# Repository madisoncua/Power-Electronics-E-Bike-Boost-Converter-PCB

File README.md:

Electric Bike Motor Boost Converter KiCad Files
Madison Cua, Tanvi Nikam, and Kellen Cao

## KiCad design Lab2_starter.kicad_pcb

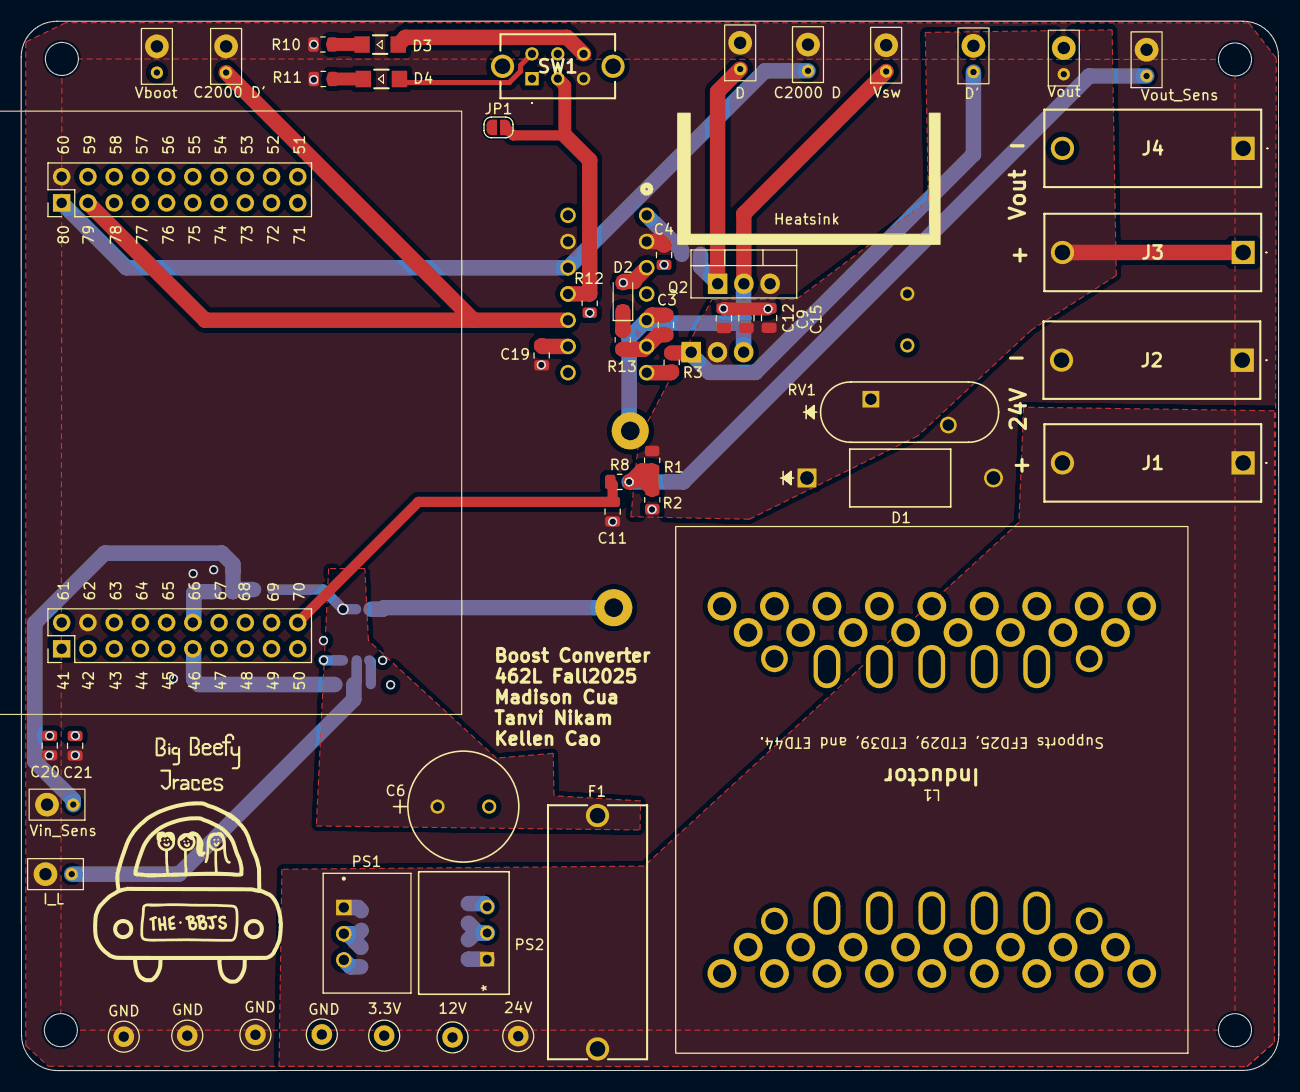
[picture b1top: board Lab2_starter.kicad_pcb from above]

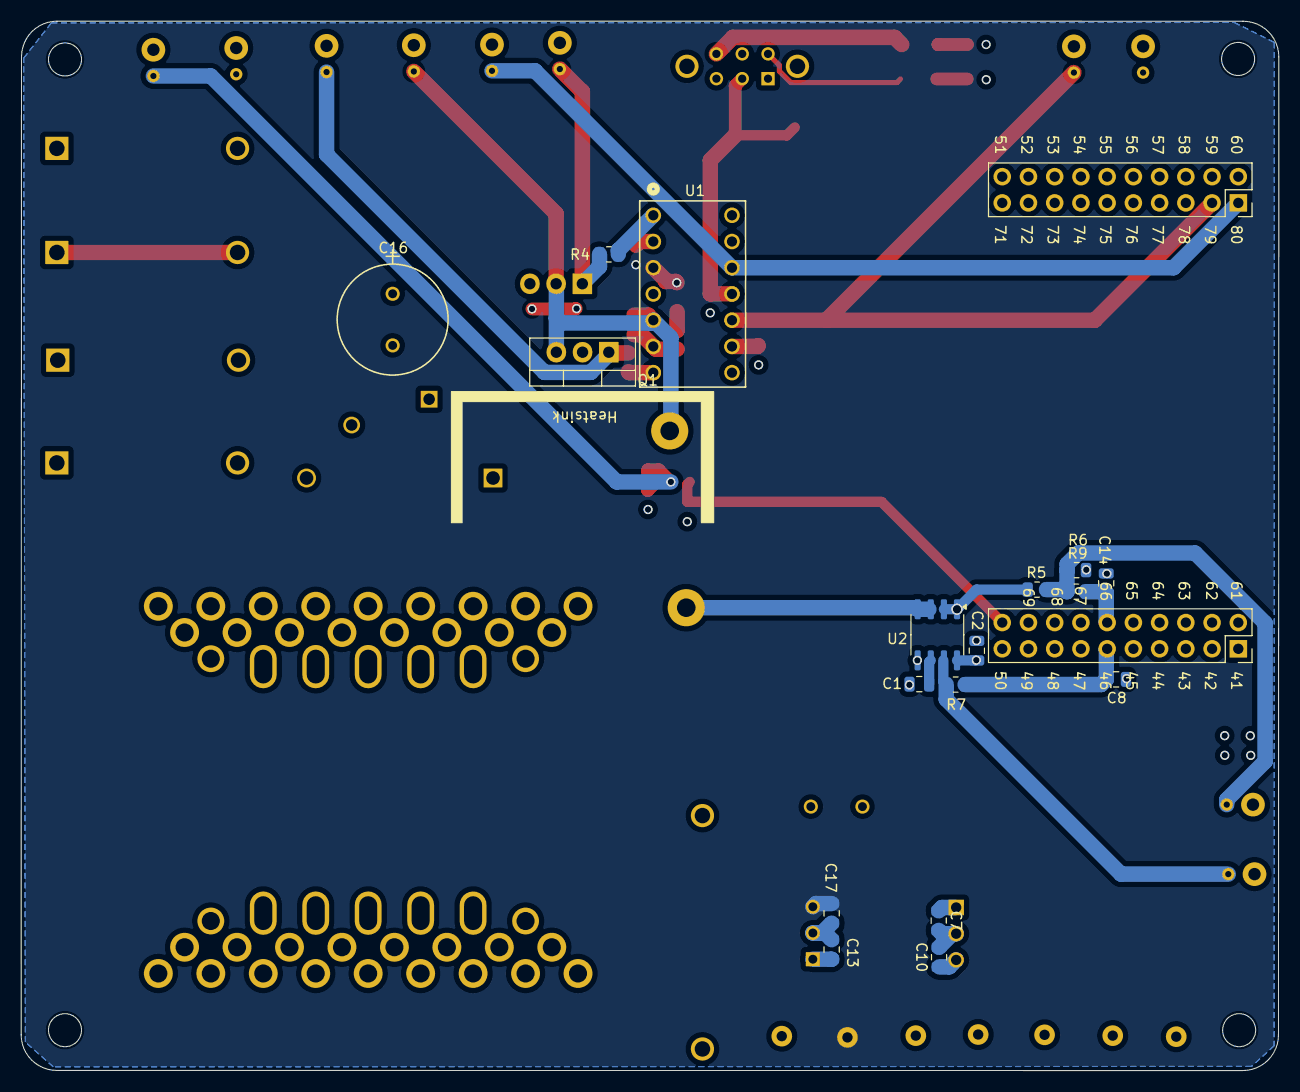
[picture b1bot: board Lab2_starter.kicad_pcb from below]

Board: 4 copper layers, 121.8 x 101.6 mm, 77 parts (18 on the bottom side), 28 nets.

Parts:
3.3V, 12V, 24V: TestPoint; TestPoint_Loop_D1.80mm_Drill1.0mm_Beaded
C1: 100 pF; C_0805_2012Metric
C2, C4, C12, C20: 0.1μF; C_0805_2012Metric
C3: C; C_0805_2012Metric
C6, C16: 100uF; 16PX2200MEFC10X20
C7, C10, C13, C17: 10uF; C_0805_2012Metric
C8, C11, C14: 1n; C_0805_2012Metric
C9: 0.01μF; C_0805_2012Metric
C15, C19, C21: 1μF; C_0805_2012Metric
C2000 D, C2000 D': Conn_01x02; TP
D: Conn_01x02; TP
D1: D_Zener; 1.5KE75A
D2: PMEG10020ELR; Nexperia_CFP3_SOD-123W
D3, D4: LED; WL-SMRW_1206_REC
D': Conn_01x02; TP
F1: Fuse; 696108003002
GND: TestPoint; TestPoint_Loop_D1.80mm_Drill1.0mm_Beaded
GND#2, GND#3, GND#4: TestPoint; TestPoint_Loop_D1.80mm_Drill1.0mm_Beaded
H1, H2, H3, H4: MountingHole; MountingHole_3.2mm_M3
HS1, HS2: Heatsink; HSS-B20-NPS-01
I_L: Conn_01x02; TP
J1, J3: 973582101
J2, J4: 973582100
J5, J6: Conn_01x01; Inductor_wire_conn
JP1: SolderJumper_2_Open; SolderJumper-2_P1.3mm_Open_RoundedPad1.0x1.5mm
L1: L; Inductor
PS1: R-78E3.3-1.0
PS2: R-78E12-0.5; R-78E-0.5_RCP
Q1, Q2: NMOS; TO-220-3_Vertical
R1: 47k; R_0805_2012Metric
R2, R6: 3.3k; R_0805_2012Metric
R3, R4: R_Small; R_0805_2012Metric
R5: 22k; R_0805_2012Metric
R7, R8, R9: 100; R_0805_2012Metric
R10, R11, R12: 1k; R_0805_2012Metric
R13: 2 Ohm; R_0805_2012Metric
RV1: Varistor; V100ZA15P
SW1: SW_Push_DPDT; SLW1116297AD
U1: IR2010; 1-2199298-3
U2: CT416-HSN820DR; SOIC-8_3.9x4.9mm_P1.27mm
U3: LAUNCHXL-F28P55X_BottomHalf
Vboot: Conn_01x02; TP
Vin_Sens: Conn_01x02; TP
Vout: Conn_01x02; TP
Vout_Sens: Conn_01x02; TP
Vsw: Conn_01x02; TP

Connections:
+3.3V: 3.3V.1, C2.1, C10.1, C19.1, C20.1, C21.1, PS1.3 (VOUT), R12.2, SW1.1 (A), SW1.5 (B), U1.9 (VDD), U2.8 (VCC), U3.41
+12V: 12V.1, C4.1, C17.1, D2.2 (A), PS2.3 (VOUT), U1.3 (VCC)
+24V: 24V.1, C7.1, C13.1, F1.1, J1.1, PS1.1 (VIN), PS2.1 (VIN)
/ADCINA0: C11.1, R8.1, U3.70
/ADCINA4: C14.1, R9.1, U3.66
/ADCINA9: C8.1, R7.1, U3.46
C2000 D: C2000 D.2, U1.12 (LIN), U3.80
C2000 D': C2000 D'.2, U1.10 (HIN), U3.79
D: D.2, Q2.1 (G), R4.2
D': D'.2, Q1.1 (G), R3.2
GND: C1.2, C2.2, C4.2, C6.2, C7.2, C8.2, C9.2, C10.2, C11.2, C12.2, C13.2, C14.2, C15.2, C16.2, C17.2, C19.2, C20.2, C21.2, C2000 D.1, C2000 D'.1, D.1, D1.2 (A), D'.1, GND.1, GND#2.1, GND#3.1, GND#4.1, I_L.1, J2.1, J4.1, PS1.2 (GND), PS2.2 (GND), Q2.3 (S), R2.2, R6.2, R10.2, R11.2, RV1.2, SW1.3 (C), U1.2 (COM), U1.13 (VSS), U2.5 (GND), U3.60, U3.62, Vboot.1, Vin_Sens.1, Vout.1, Vout_Sens.1, Vsw.1
I_L: I_L.2, R7.2, U2.7 (OUT)
unnamed: D2.1 (K), R13.1
unnamed: D3.2 (A), SW1.4 (A)
unnamed: D3.1 (K), R10.1
unnamed: D4.2 (A), SW1.6 (C)
unnamed: D4.1 (K), R11.1
unnamed: J6.1, U2.3 (IP-), U2.4 (IP-)
unnamed: R3.1, U1.7 (HO)
unnamed: R4.1, U1.1 (LO)
unnamed: C1.1, U2.6 (FILTER)
SD: JP1.2 (B), R12.1, SW1.2 (B), U1.11 (SD)
Vboot: C3.1, R13.2, U1.6 (VB), Vboot.2
Vin: C6.1, F1.2, R5.1, U2.1 (IP+), U2.2 (IP+)
Vin_sens: R5.2, R6.1, R9.2, Vin_Sens.2
Vout: C9.1, C12.1, C15.1, C16.1, D1.1 (K), J3.1, Q1.2 (D), R1.1, RV1.1, Vout.2
Vout_sens: R1.2, R2.1, R8.2, Vout_Sens.2
Vsw: C3.2, J5.1, Q1.3 (S), Q2.2 (D), U1.5 (VS), Vsw.2

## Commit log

2025-09-19 Initial commit of KiCad project
2025-09-20 Add Kicad files
2025-09-20 Moved components around
2025-09-20 Fixed gitignore
2025-09-21 Bring over gating loop items
2025-09-21 Creating gating loop
2025-09-24 Fixed gating loop
2025-09-26 Everything
2025-09-28 Edge Cuts + Test Points
    Edge cuts, tucked right PCB edge in, moved test points and redid the test point routing for cleanliness
2025-09-28 Added planes and fixed for DRC
2025-09-29 Fix high didt pathways
2025-09-29 Silk Screen
2025-09-30 Ground , sw cutout zone
2025-09-30 Ground cutout
2025-09-30 Fixed ADC
2025-10-01 Fixed filled zones
2025-10-01 Final push
2025-10-03 Fixed Aisler DRC
2025-10-03 All changes
2025-10-03 Fixed Uneven copper distribution
2025-10-03 Added solid ground plane on top layer (prio 0)
2025-10-15 Updated component library

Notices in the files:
parts and their libraries:
Copyright 2016 Accelerated Designs. All rights reserved.
